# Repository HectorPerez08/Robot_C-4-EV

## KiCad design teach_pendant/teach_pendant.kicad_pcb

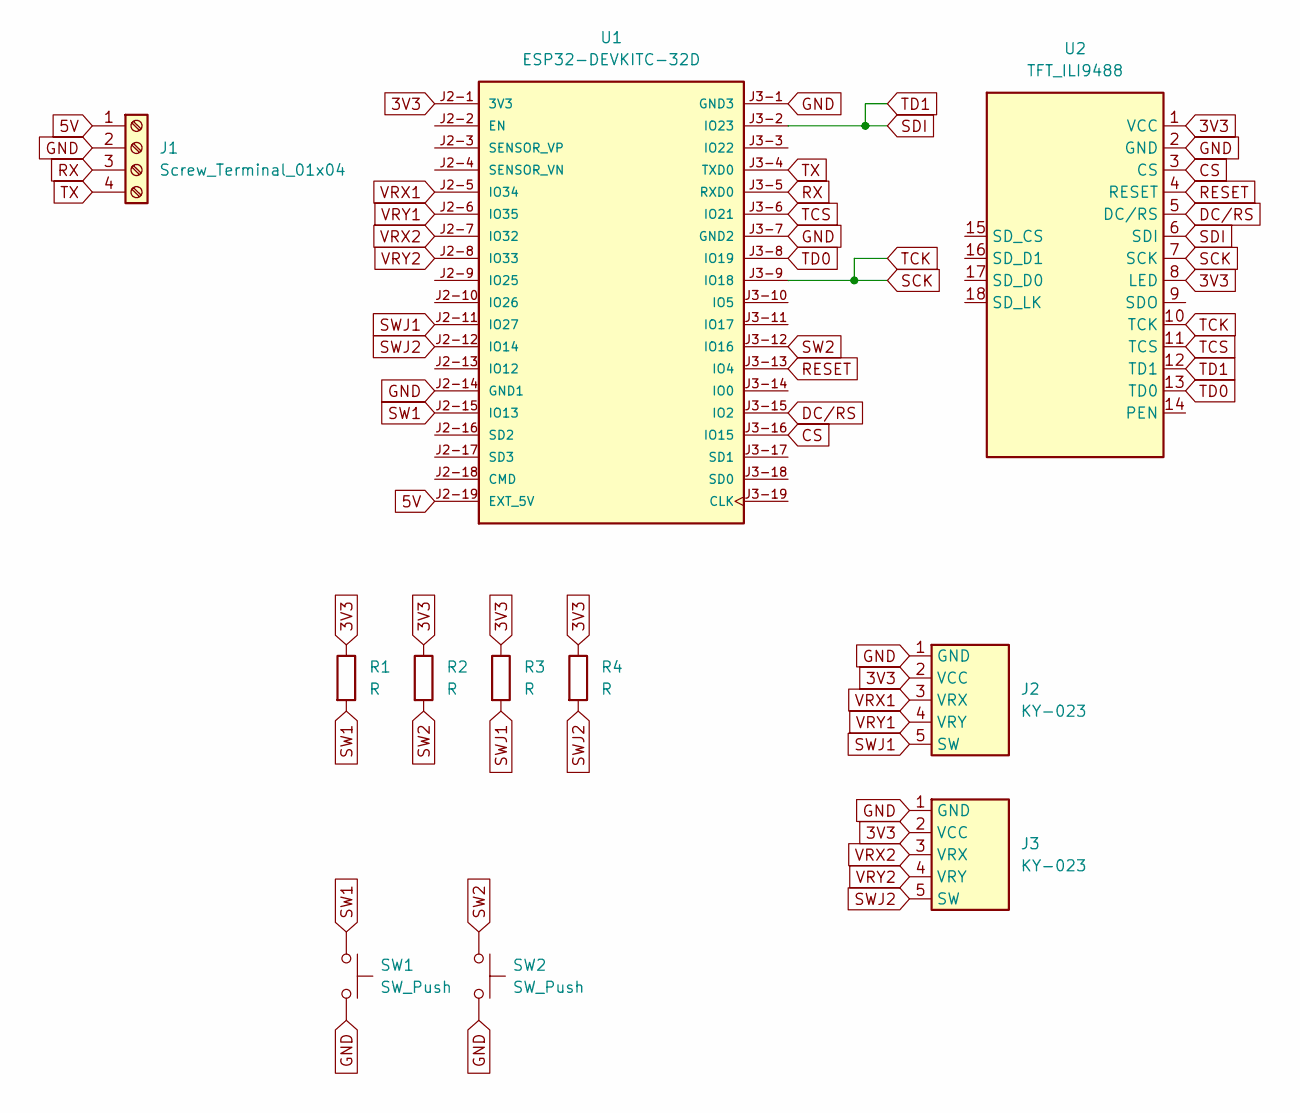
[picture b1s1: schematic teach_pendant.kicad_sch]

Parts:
J1: Screw_Terminal_01x04; TerminalBlock_Phoenix_MKDS-1,5-4-5.08_1x04_P5.08mm_Horizont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
J2, J3: KY-023; KY-023 Joystick-Module
R1, R2, R3, R4: R; R_Axial_DIN0207_L6.3mm_D2.5mm_P7.62mm_Horizontal
SW1, SW2: SW_Push; SW_FSM8JH_huella
U1: ESP32-DEVKITC-32D; MODULE_ESP32-DEVKITC-32D; PARTREV V4
U2: TFT_ILI9488

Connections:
3V3: J2.2 (VCC), J3.2 (VCC), R1.1, R2.1, R3.1, R4.1, U1.J2-1 (3V3), U2.1 (VCC), U2.8 (LED)
5V: J1.1, U1.J2-19 (EXT_5V)
CS: U1.J3-16 (IO15), U2.3 (CS)
DC/RS: U1.J3-15 (IO2), U2.5 (DC/RS)
GND: J1.2, J2.1 (GND), J3.1 (GND), SW1.2, SW2.2, U1.J2-14 (GND1), U1.J3-1 (GND3), U1.J3-7 (GND2), U2.2 (GND)
RESET: U1.J3-13 (IO4), U2.4 (RESET)
RX: J1.3, U1.J3-5 (RXD0)
SCK: U1.J3-9 (IO18), U2.7 (SCK), U2.10 (TCK)
SDI: U1.J3-2 (IO23), U2.6 (SDI), U2.12 (TD1)
SW1: R1.2, SW1.1, U1.J2-15 (IO13)
SW2: R2.2, SW2.1, U1.J3-12 (IO16)
SWJ1: J2.5 (SW), R3.2, U1.J2-11 (IO27)
SWJ2: J3.5 (SW), R4.2, U1.J2-12 (IO14)
TCS: U1.J3-6 (IO21), U2.11 (TCS)
TD0: U1.J3-8 (IO19), U2.13 (TD0)
TX: J1.4, U1.J3-4 (TXD0)
VRX1: J2.3 (VRX), U1.J2-5 (IO34)
VRX2: J3.3 (VRX), U1.J2-7 (IO32)
VRY1: J2.4 (VRY), U1.J2-6 (IO35)
VRY2: J3.4 (VRY), U1.J2-8 (IO33)

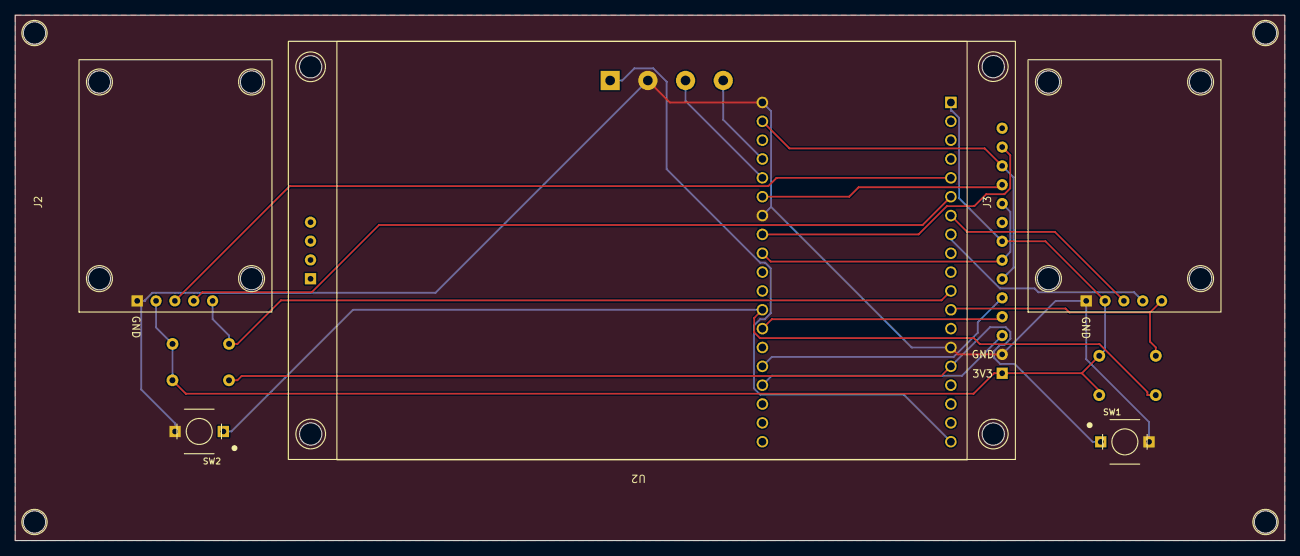
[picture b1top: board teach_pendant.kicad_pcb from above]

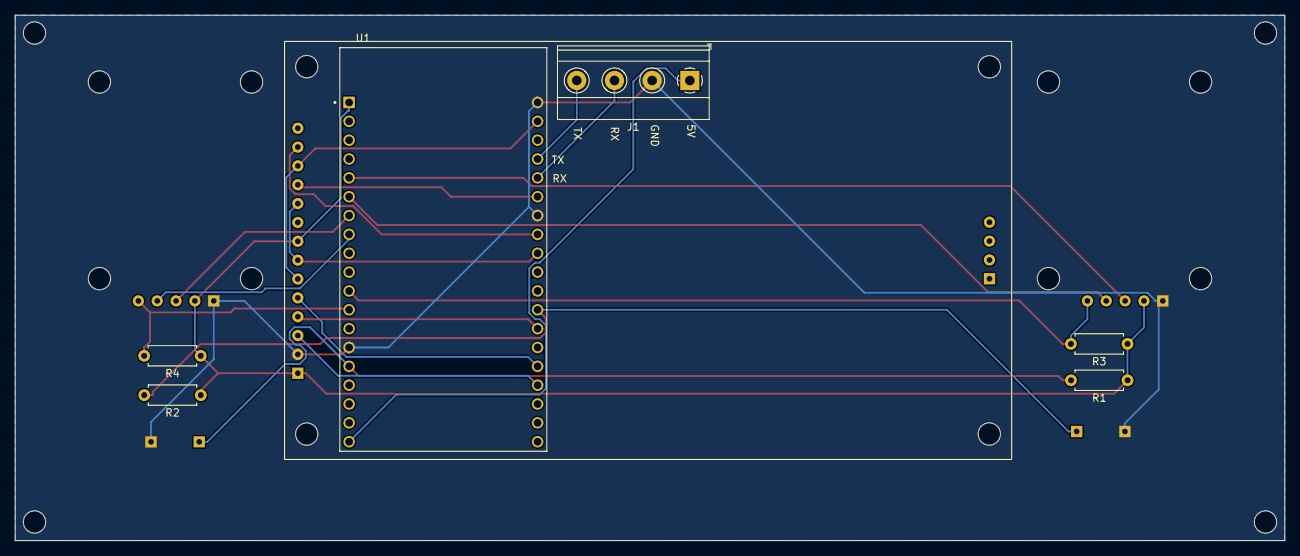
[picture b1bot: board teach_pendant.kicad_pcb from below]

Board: 2 copper layers, 171.1 x 70.8 mm, 11 parts (6 on the bottom side), 20 nets.

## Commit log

2024-06-30 Se agrega el proyecto
2024-07-21 agrego funcion boton de paro y librerias necesarias
